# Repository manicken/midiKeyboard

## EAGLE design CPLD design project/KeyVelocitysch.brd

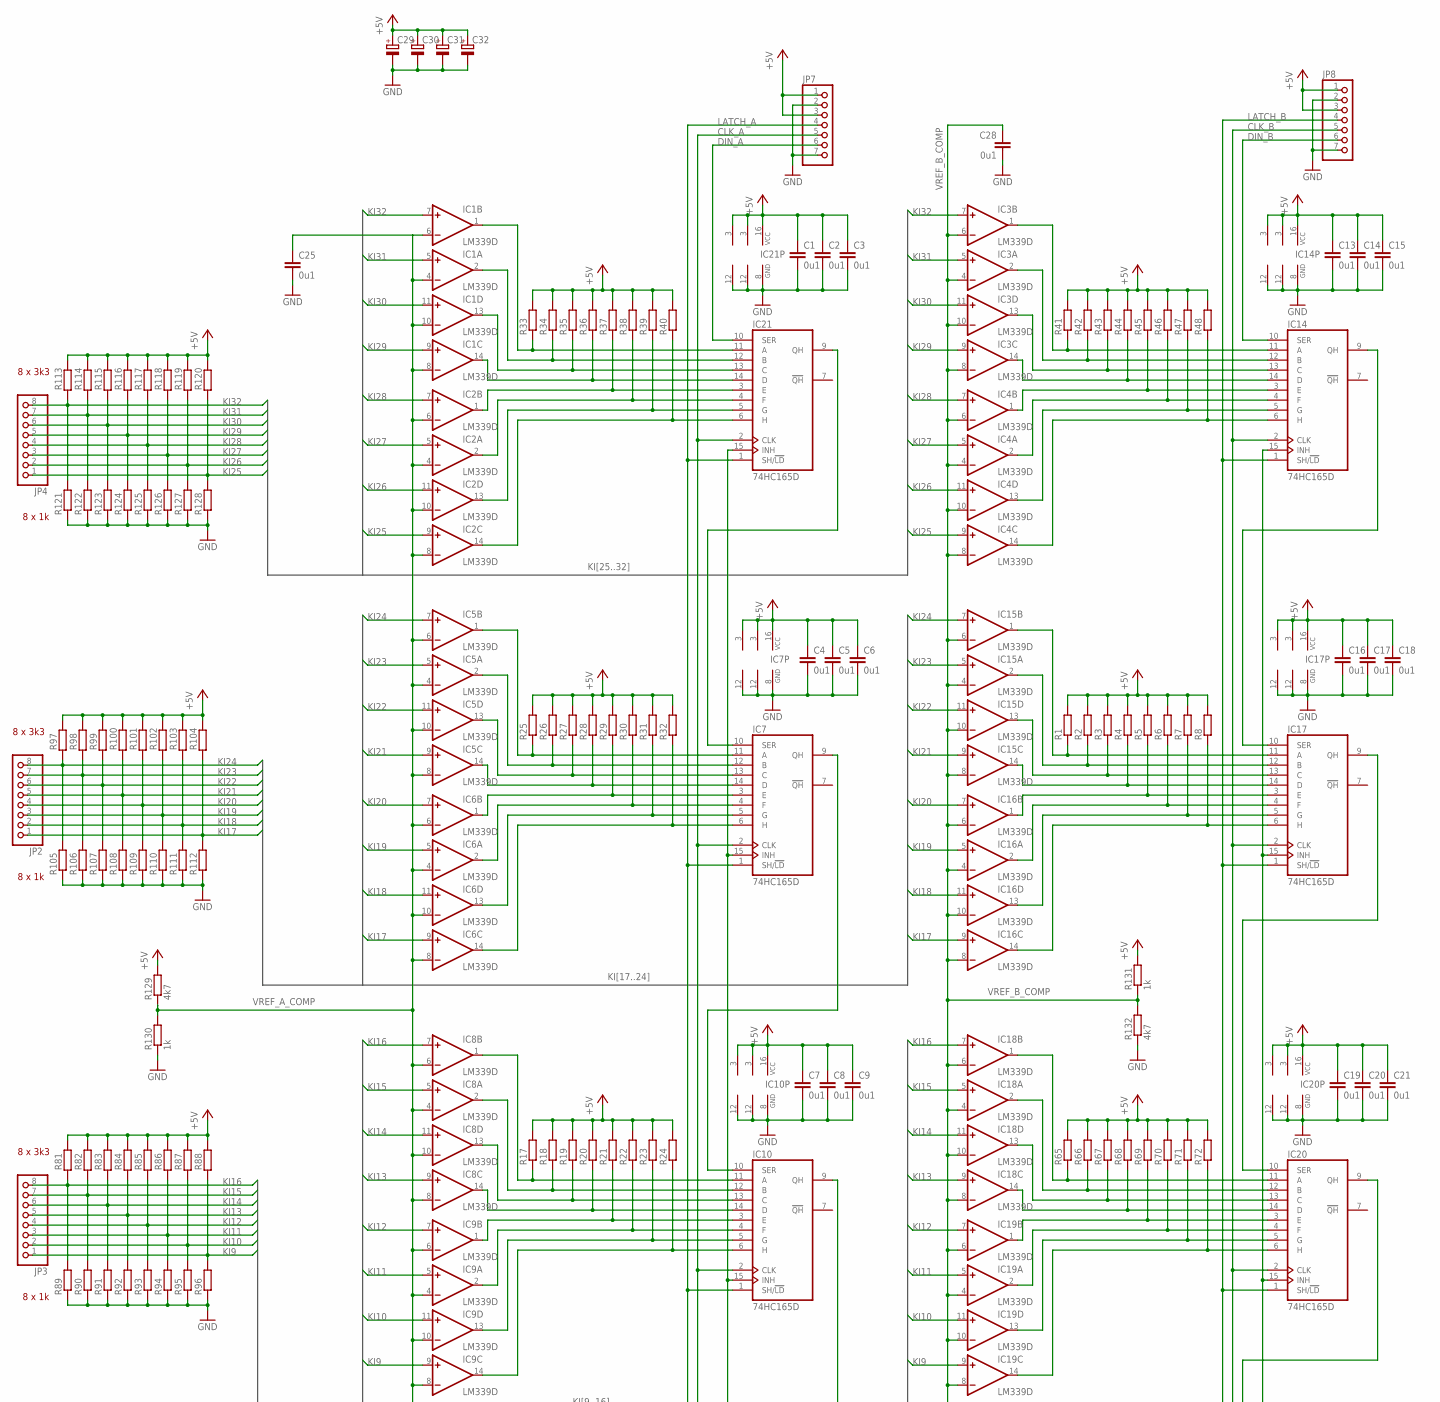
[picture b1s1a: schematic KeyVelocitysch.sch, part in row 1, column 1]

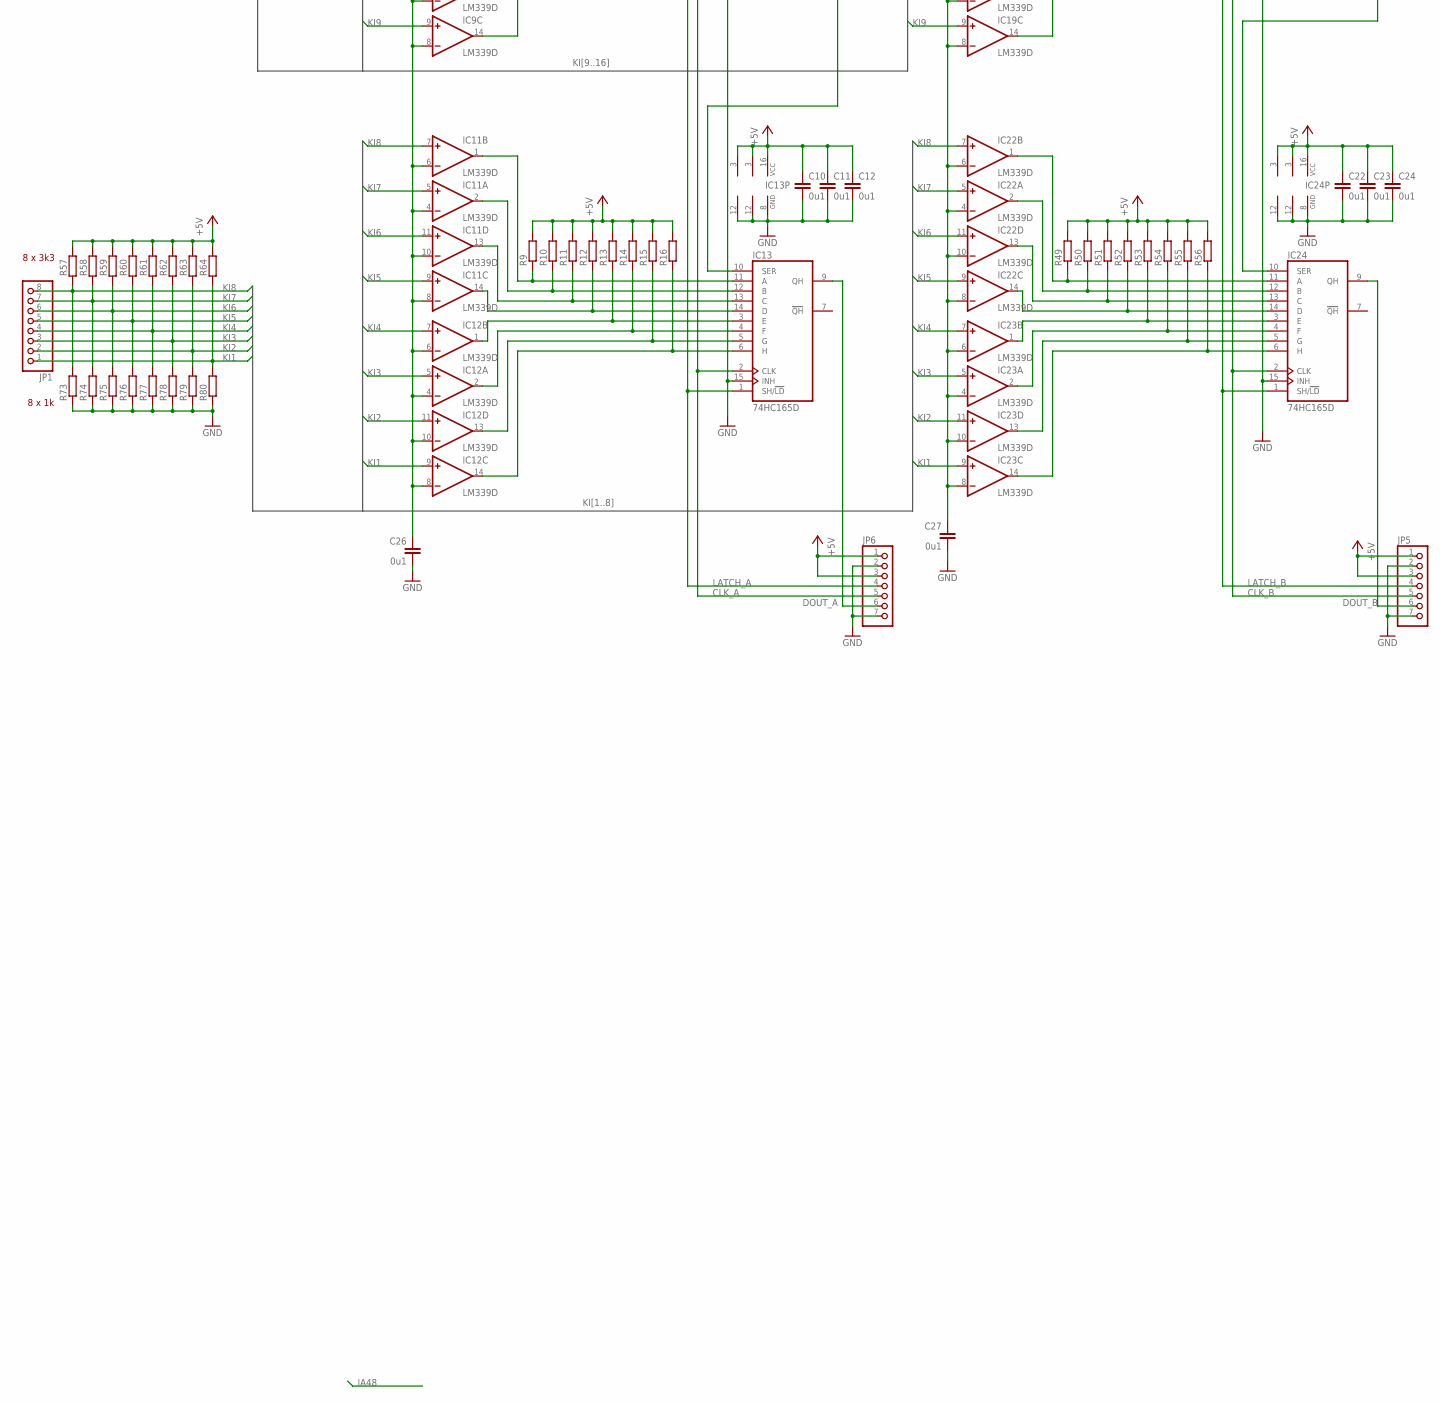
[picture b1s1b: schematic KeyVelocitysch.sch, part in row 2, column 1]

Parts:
C1, C2, C3, C4, C5, C6, C7, C8, C9, C10, C11, C12, C13, C14, C15, C16, C17, C18, C19, C20, C21, C22, C23, C24, C25, C26, C27, C28: 0u1; C0603
C29, C30, C31, C32: CPOL-EUE2.5-5; E2,5-5
IC1, IC2, IC3, IC4, IC5, IC6, IC8, IC9, IC11, IC12, IC15, IC16, IC18, IC19, IC22, IC23: LM339D; SO14
IC7, IC10, IC13, IC14, IC17, IC20, IC21, IC24: 74HC165D; SO16
JP1, JP2, JP3, JP4: PINHD-1X8; 1X08
JP5, JP6, JP7, JP8: PINHD-1X7; 1X07
R1, R2, R3, R4, R5, R6, R7, R8, R9, R10, R11, R12, R13, R14, R15, R16, R17, R18, R19, R20, R21, R22, R23, R24, R25, R26, R27, R28, R29, R30, R31, R32, R33, R34, R35, R36, R37, R38, R39, R40, R41, R42, R43, R44, R45, R46, R47, R48, R49, R50, R51, R52, R53, R54, R55, R56, R65, R66, R67, R68, R69, R70, R71, R72: R-EU_R0402; R0402
R57, R58, R59, R60, R61, R62, R63, R64, R73, R74, R75, R76, R77, R78, R79, R80, R81, R82, R83, R84, R85, R86, R87, R88, R89, R90, R91, R92, R93, R94, R95, R96, R97, R98, R99, R100, R101, R102, R103, R104, R105, R106, R107, R108, R109, R110, R111, R112, R113, R114, R115, R116, R117, R118, R119, R120, R121, R122, R123, R124, R125, R126, R127, R128: R-EU_R0603; R0603
R129, R132: 4k7; R0603
R130, R131: 1k; R0603

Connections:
+5V: C1.1, C2.1, C3.1, C4.1, C5.1, C6.1, C7.1, C8.1, C9.1, C10.1, C11.1, C12.1, C13.1, C14.1, C15.1, C16.1, C17.1, C18.1, C19.1, C20.1, C21.1, C22.1, C23.1, C24.1, C29.+, C30.+, C31.+, C32.+, IC1.3 (V+), IC2.3 (V+), IC3.3 (V+), IC4.3 (V+), IC5.3 (V+), IC6.3 (V+), IC7.16 (VCC), IC8.3 (V+), IC9.3 (V+), IC10.16 (VCC), IC11.3 (V+), IC12.3 (V+), IC13.16 (VCC), IC14.16 (VCC), IC15.3 (V+), IC16.3 (V+), IC17.16 (VCC), IC18.3 (V+), IC19.3 (V+), IC20.16 (VCC), IC21.16 (VCC), IC22.3 (V+), IC23.3 (V+), IC24.16 (VCC), JP5.1, JP5.3, JP6.1, JP6.3, JP7.1, JP7.3, JP8.1, JP8.3, R1.2, R2.2, R3.2, R4.2, R5.2, R6.2, R7.2, R8.2, R9.2, R10.2, R11.2, R12.2, R13.2, R14.2, R15.2, R16.2, R17.2, R18.2, R19.2, R20.2, R21.2, R22.2, R23.2, R24.2, R25.2, R26.2, R27.2, R28.2, R29.2, R30.2, R31.2, R32.2, R33.2, R34.2, R35.2, R36.2, R37.2, R38.2, R39.2, R40.2, R41.2, R42.2, R43.2, R44.2, R45.2, R46.2, R47.2, R48.2, R49.2, R50.2, R51.2, R52.2, R53.2, R54.2, R55.2, R56.2, R57.2, R58.2, R59.2, R60.2, R61.2, R62.2, R63.2, R64.2, R65.2, R66.2, R67.2, R68.2, R69.2, R70.2, R71.2, R72.2, R81.2, R82.2, R83.2, R84.2, R85.2, R86.2, R87.2, R88.2, R97.2, R98.2, R99.2, R100.2, R101.2, R102.2, R103.2, R104.2, R113.2, R114.2, R115.2, R116.2, R117.2, R118.2, R119.2, R120.2, R129.2, R131.2
CLK_A: IC7.2 (CLK), IC10.2 (CLK), IC13.2 (CLK), IC21.2 (CLK), JP6.5, JP7.5
CLK_B: IC14.2 (CLK), IC17.2 (CLK), IC20.2 (CLK), IC24.2 (CLK), JP5.5, JP8.5
DA1: IC12.14 (OUT), IC13.6 (H), R16.1
DA8: IC11.1 (OUT), IC13.11 (A), R9.1
DA9: IC9.14 (OUT), IC10.6 (H), R24.1
DA16: IC8.1 (OUT), IC10.11 (A), R17.1
DA17: IC6.14 (OUT), IC7.6 (H), R32.1
DA24: IC5.1 (OUT), IC7.11 (A), R25.1
DA25: IC2.14 (OUT), IC21.6 (H), R40.1
DA32: IC1.1 (OUT), IC21.11 (A), R33.1
DB1: IC23.14 (OUT), IC24.6 (H), R56.1
DB8: IC22.1 (OUT), IC24.11 (A), R49.1
DB9: IC19.14 (OUT), IC20.6 (H), R72.1
DB16: IC18.1 (OUT), IC20.11 (A), R65.1
DB17: IC16.14 (OUT), IC17.6 (H), R8.1
DB24: IC15.1 (OUT), IC17.11 (A), R1.1
DB25: IC4.14 (OUT), IC14.6 (H), R48.1
DB32: IC3.1 (OUT), IC14.11 (A), R41.1
DIN_A: IC21.10 (SER), JP7.6
DIN_B: IC14.10 (SER), JP8.6
DOUT_A: IC13.9 (QH), JP6.6
DOUT_B: IC24.9 (QH), JP5.6
GND: C1.2, C2.2, C3.2, C4.2, C5.2, C6.2, C7.2, C8.2, C9.2, C10.2, C11.2, C12.2, C13.2, C14.2, C15.2, C16.2, C17.2, C18.2, C19.2, C20.2, C21.2, C22.2, C23.2, C24.2, C25.2, C26.2, C27.2, C28.2, C29.-, C30.-, C31.-, C32.-, IC1.12 (GND), IC2.12 (GND), IC3.12 (GND), IC4.12 (GND), IC5.12 (GND), IC6.12 (GND), IC7.8 (GND), IC7.15 (INH), IC8.12 (GND), IC9.12 (GND), IC10.8 (GND), IC10.15 (INH), IC11.12 (GND), IC12.12 (GND), IC13.8 (GND), IC13.15 (INH), IC14.8 (GND), IC14.15 (INH), IC15.12 (GND), IC16.12 (GND), IC17.8 (GND), IC17.15 (INH), IC18.12 (GND), IC19.12 (GND), IC20.8 (GND), IC20.15 (INH), IC21.8 (GND), IC21.15 (INH), IC22.12 (GND), IC23.12 (GND), IC24.8 (GND), IC24.15 (INH), JP5.2, JP5.7, JP6.2, JP6.7, JP7.2, JP7.7, JP8.2, JP8.7, R73.1, R74.1, R75.1, R76.1, R77.1, R78.1, R79.1, R80.1, R89.1, R90.1, R91.1, R92.1, R93.1, R94.1, R95.1, R96.1, R105.1, R106.1, R107.1, R108.1, R109.1, R110.1, R111.1, R112.1, R121.1, R122.1, R123.1, R124.1, R125.1, R126.1, R127.1, R128.1, R130.1, R132.1
KI1: IC12.9 (+IN), IC23.9 (+IN), JP1.1, R64.1, R80.2
KI2: IC12.11 (+IN), IC23.11 (+IN), JP1.2, R63.1, R79.2
KI3: IC12.5 (+IN), IC23.5 (+IN), JP1.3, R62.1, R78.2
KI4: IC12.7 (+IN), IC23.7 (+IN), JP1.4, R61.1, R77.2
KI5: IC11.9 (+IN), IC22.9 (+IN), JP1.5, R60.1, R76.2
KI6: IC11.11 (+IN), IC22.11 (+IN), JP1.6, R59.1, R75.2
KI7: IC11.5 (+IN), IC22.5 (+IN), JP1.7, R58.1, R74.2
KI8: IC11.7 (+IN), IC22.7 (+IN), JP1.8, R57.1, R73.2
KI9: IC9.9 (+IN), IC19.9 (+IN), JP3.1, R88.1, R96.2
KI10: IC9.11 (+IN), IC19.11 (+IN), JP3.2, R87.1, R95.2
KI11: IC9.5 (+IN), IC19.5 (+IN), JP3.3, R86.1, R94.2
KI12: IC9.7 (+IN), IC19.7 (+IN), JP3.4, R85.1, R93.2
KI13: IC8.9 (+IN), IC18.9 (+IN), JP3.5, R84.1, R92.2
KI14: IC8.11 (+IN), IC18.11 (+IN), JP3.6, R83.1, R91.2
KI15: IC8.5 (+IN), IC18.5 (+IN), JP3.7, R82.1, R90.2
KI16: IC8.7 (+IN), IC18.7 (+IN), JP3.8, R81.1, R89.2
KI17: IC6.9 (+IN), IC16.9 (+IN), JP2.1, R104.1, R112.2
KI18: IC6.11 (+IN), IC16.11 (+IN), JP2.2, R103.1, R111.2
KI19: IC6.5 (+IN), IC16.5 (+IN), JP2.3, R102.1, R110.2
KI20: IC6.7 (+IN), IC16.7 (+IN), JP2.4, R101.1, R109.2
KI21: IC5.9 (+IN), IC15.9 (+IN), JP2.5, R100.1, R108.2
KI22: IC5.11 (+IN), IC15.11 (+IN), JP2.6, R99.1, R107.2
KI23: IC5.5 (+IN), IC15.5 (+IN), JP2.7, R98.1, R106.2
KI24: IC5.7 (+IN), IC15.7 (+IN), JP2.8, R97.1, R105.2
KI25: IC2.9 (+IN), IC4.9 (+IN), JP4.1, R120.1, R128.2
KI26: IC2.11 (+IN), IC4.11 (+IN), JP4.2, R119.1, R127.2
KI27: IC2.5 (+IN), IC4.5 (+IN), JP4.3, R118.1, R126.2
KI28: IC2.7 (+IN), IC4.7 (+IN), JP4.4, R117.1, R125.2
KI29: IC1.9 (+IN), IC3.9 (+IN), JP4.5, R116.1, R124.2
KI30: IC1.11 (+IN), IC3.11 (+IN), JP4.6, R115.1, R123.2
KI31: IC1.5 (+IN), IC3.5 (+IN), JP4.7, R114.1, R122.2
KI32: IC1.7 (+IN), IC3.7 (+IN), JP4.8, R113.1, R121.2
LATCH_A: IC7.1 (SH/!LD), IC10.1 (SH/!LD), IC13.1 (SH/!LD), IC21.1 (SH/!LD), JP6.4, JP7.4
LATCH_B: IC14.1 (SH/!LD), IC17.1 (SH/!LD), IC20.1 (SH/!LD), IC24.1 (SH/!LD), JP5.4, JP8.4
unnamed: IC14.9 (QH), IC17.10 (SER)
unnamed: IC17.9 (QH), IC20.10 (SER)
unnamed: IC12.13 (OUT), IC13.5 (G), R15.1
unnamed: IC20.9 (QH), IC24.10 (SER)
unnamed: IC12.2 (OUT), IC13.4 (F), R14.1
unnamed: IC12.1 (OUT), IC13.3 (E), R13.1
unnamed: IC11.14 (OUT), IC13.14 (D), R12.1
unnamed: IC7.10 (SER), IC21.9 (QH)
unnamed: IC11.13 (OUT), IC13.13 (C), R11.1
unnamed: IC11.2 (OUT), IC13.12 (B), R10.1
unnamed: IC8.2 (OUT), IC10.12 (B), R18.1
unnamed: IC8.13 (OUT), IC10.13 (C), R19.1
unnamed: IC8.14 (OUT), IC10.14 (D), R20.1
unnamed: IC9.1 (OUT), IC10.3 (E), R21.1
unnamed: IC9.2 (OUT), IC10.4 (F), R22.1
unnamed: IC7.9 (QH), IC10.10 (SER)
unnamed: IC9.13 (OUT), IC10.5 (G), R23.1
unnamed: IC10.9 (QH), IC13.10 (SER)
unnamed: IC5.2 (OUT), IC7.12 (B), R26.1
unnamed: IC5.13 (OUT), IC7.13 (C), R27.1
unnamed: IC5.14 (OUT), IC7.14 (D), R28.1
unnamed: IC6.1 (OUT), IC7.3 (E), R29.1
unnamed: IC6.2 (OUT), IC7.4 (F), R30.1
unnamed: IC6.13 (OUT), IC7.5 (G), R31.1
unnamed: IC1.2 (OUT), IC21.12 (B), R34.1
unnamed: IC1.13 (OUT), IC21.13 (C), R35.1
unnamed: IC1.14 (OUT), IC21.14 (D), R36.1
unnamed: IC2.1 (OUT), IC21.3 (E), R37.1
unnamed: IC2.2 (OUT), IC21.4 (F), R38.1
unnamed: IC2.13 (OUT), IC21.5 (G), R39.1
unnamed: IC22.2 (OUT), IC24.12 (B), R50.1
unnamed: IC22.13 (OUT), IC24.13 (C), R51.1
unnamed: IC22.14 (OUT), IC24.14 (D), R52.1
unnamed: IC23.1 (OUT), IC24.3 (E), R53.1
unnamed: IC23.2 (OUT), IC24.4 (F), R54.1
unnamed: IC23.13 (OUT), IC24.5 (G), R55.1
unnamed: IC18.2 (OUT), IC20.12 (B), R66.1
unnamed: IC18.13 (OUT), IC20.13 (C), R67.1
unnamed: IC18.14 (OUT), IC20.14 (D), R68.1
unnamed: IC19.1 (OUT), IC20.3 (E), R69.1
unnamed: IC19.2 (OUT), IC20.4 (F), R70.1
unnamed: IC19.13 (OUT), IC20.5 (G), R71.1
unnamed: IC15.2 (OUT), IC17.12 (B), R2.1
unnamed: IC15.13 (OUT), IC17.13 (C), R3.1
unnamed: IC15.14 (OUT), IC17.14 (D), R4.1
unnamed: IC16.1 (OUT), IC17.3 (E), R5.1
unnamed: IC16.2 (OUT), IC17.4 (F), R6.1
unnamed: IC16.13 (OUT), IC17.5 (G), R7.1
unnamed: IC3.2 (OUT), IC14.12 (B), R42.1
unnamed: IC3.13 (OUT), IC14.13 (C), R43.1
unnamed: IC3.14 (OUT), IC14.14 (D), R44.1
unnamed: IC4.1 (OUT), IC14.3 (E), R45.1
unnamed: IC4.2 (OUT), IC14.4 (F), R46.1
unnamed: IC4.13 (OUT), IC14.5 (G), R47.1
VREF_A_COMP: C25.1, C26.1, IC1.4 (-IN), IC1.6 (-IN), IC1.8 (-IN), IC1.10 (-IN), IC2.4 (-IN), IC2.6 (-IN), IC2.8 (-IN), IC2.10 (-IN), IC5.4 (-IN), IC5.6 (-IN), IC5.8 (-IN), IC5.10 (-IN), IC6.4 (-IN), IC6.6 (-IN), IC6.8 (-IN), IC6.10 (-IN), IC8.4 (-IN), IC8.6 (-IN), IC8.8 (-IN), IC8.10 (-IN), IC9.4 (-IN), IC9.6 (-IN), IC9.8 (-IN), IC9.10 (-IN), IC11.4 (-IN), IC11.6 (-IN), IC11.8 (-IN), IC11.10 (-IN), IC12.4 (-IN), IC12.6 (-IN), IC12.8 (-IN), IC12.10 (-IN), R129.1, R130.2
VREF_B_COMP: C27.1, C28.1, IC3.4 (-IN), IC3.6 (-IN), IC3.8 (-IN), IC3.10 (-IN), IC4.4 (-IN), IC4.6 (-IN), IC4.8 (-IN), IC4.10 (-IN), IC15.4 (-IN), IC15.6 (-IN), IC15.8 (-IN), IC15.10 (-IN), IC16.4 (-IN), IC16.6 (-IN), IC16.8 (-IN), IC16.10 (-IN), IC18.4 (-IN), IC18.6 (-IN), IC18.8 (-IN), IC18.10 (-IN), IC19.4 (-IN), IC19.6 (-IN), IC19.8 (-IN), IC19.10 (-IN), IC22.4 (-IN), IC22.6 (-IN), IC22.8 (-IN), IC22.10 (-IN), IC23.4 (-IN), IC23.6 (-IN), IC23.8 (-IN), IC23.10 (-IN), R131.1, R132.2

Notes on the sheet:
8 x 3k3
8 x 1k

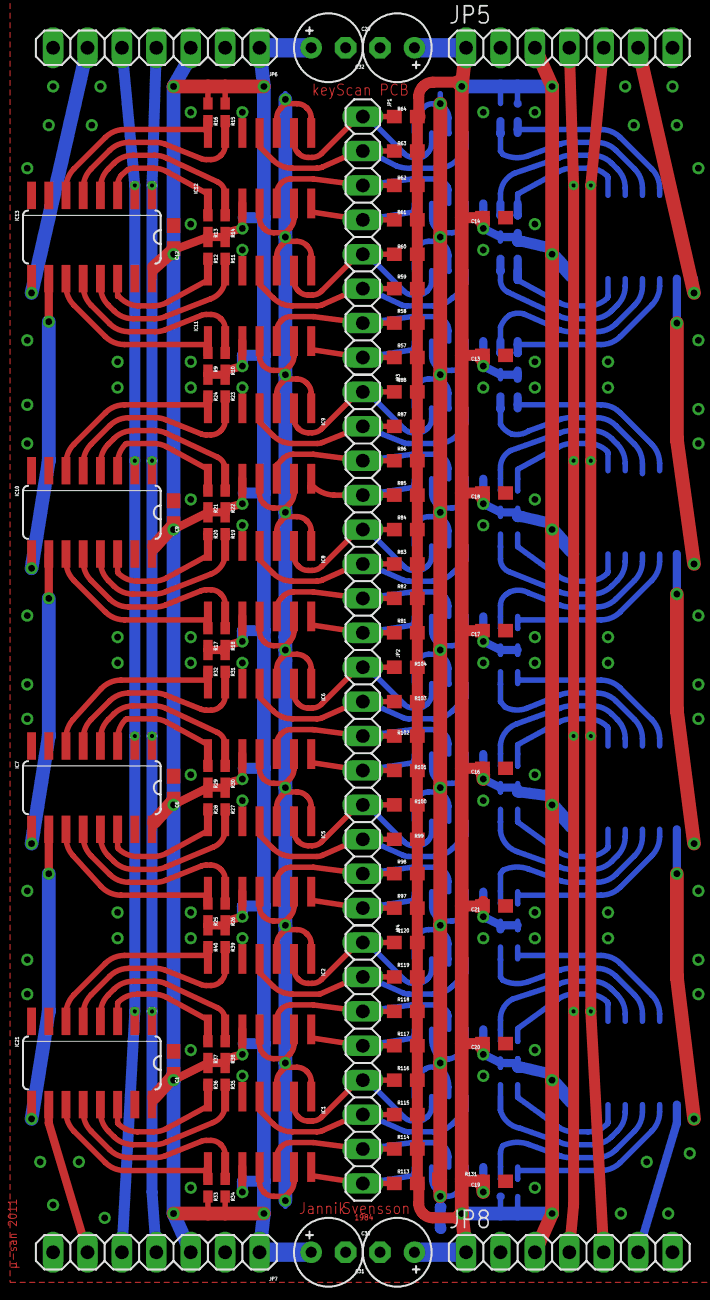
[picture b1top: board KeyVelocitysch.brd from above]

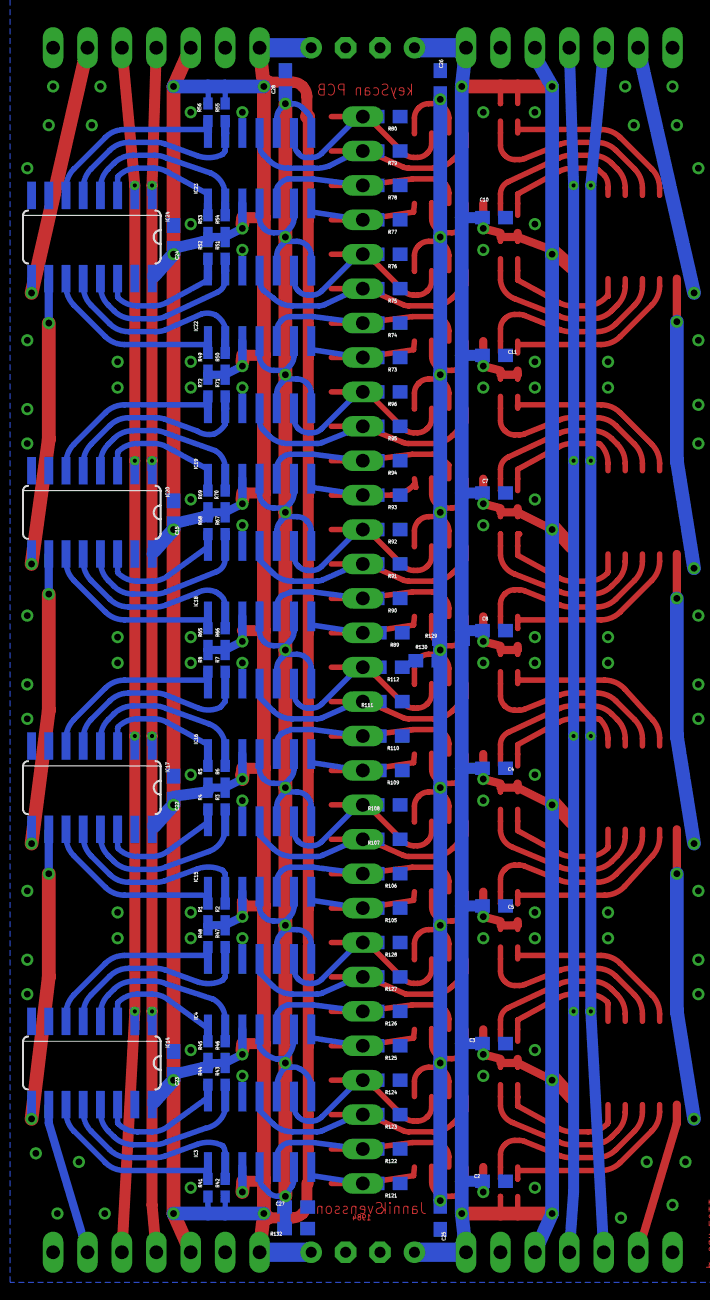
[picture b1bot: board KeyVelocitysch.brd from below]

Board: 2 copper layers, 196 parts (95 on the bottom side), 114 nets.

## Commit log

2021-11-16 add layout + fix folders
2021-11-16 forgot layout files
2021-11-16 add complete quartus ii project
2021-11-16 add readme
2021-11-16 readme add images
2021-11-16 crop image
2021-11-16 add image
